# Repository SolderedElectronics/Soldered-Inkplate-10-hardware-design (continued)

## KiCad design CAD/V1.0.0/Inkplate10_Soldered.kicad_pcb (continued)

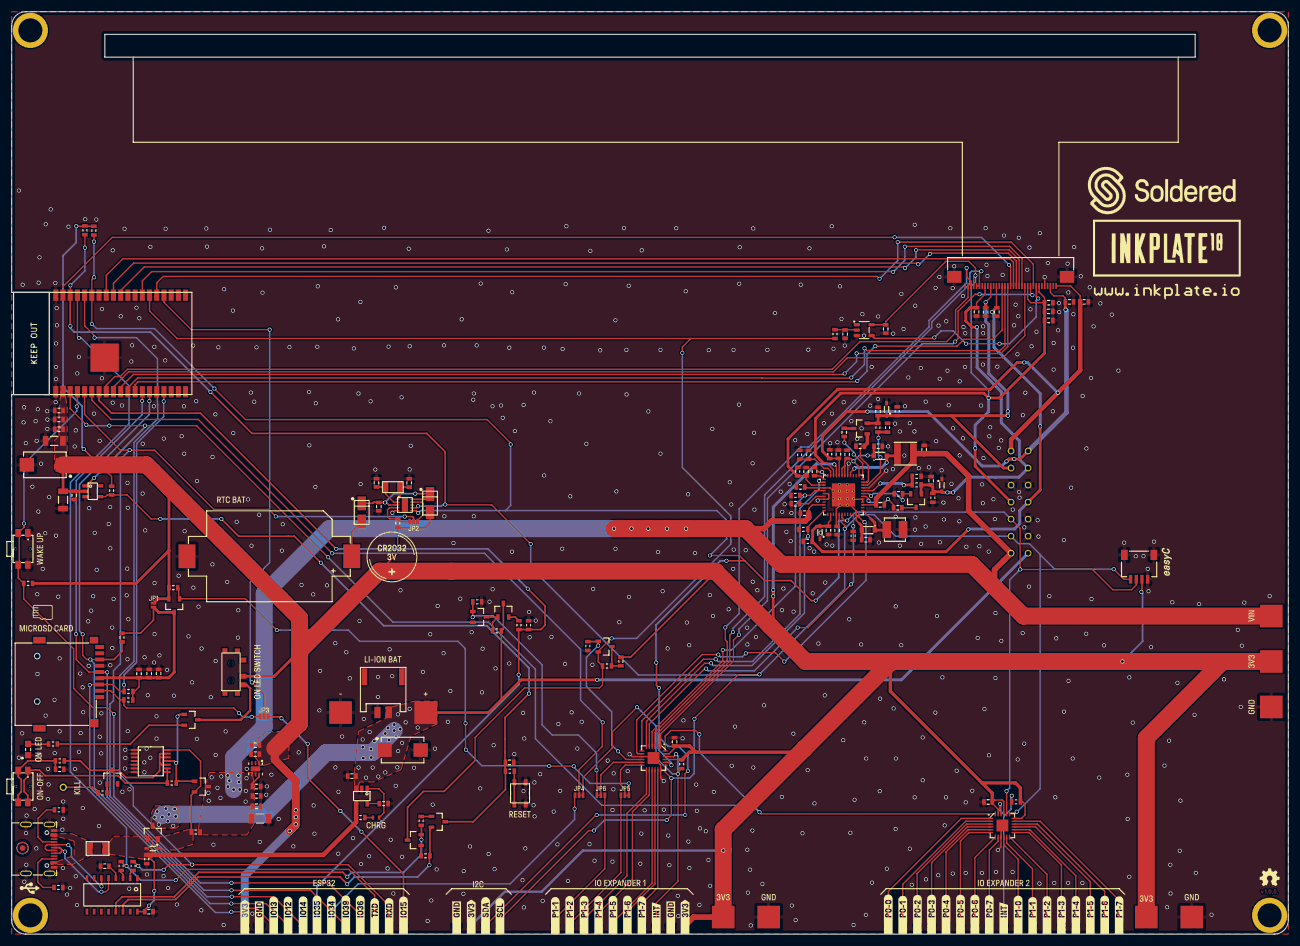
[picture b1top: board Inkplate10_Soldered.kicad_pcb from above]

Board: 2 copper layers, 224.8 x 162.4 mm, 290 parts (1 on the bottom side), 131 nets.

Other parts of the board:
Ref**: Val**; Version1.0.0.
kibuzzard-62EA6F76: G***; kibuzzard-62EA6F76
kibuzzard-62EA6FEE: G***; kibuzzard-62EA6FEE
kibuzzard-62EA71AD: G***; kibuzzard-62EA71AD
kibuzzard-62EA71BF: G***; kibuzzard-62EA71BF
kibuzzard-62EA71CF: G***; kibuzzard-62EA71CF
kibuzzard-62EA72A0: G***; kibuzzard-62EA72A0
kibuzzard-62EA72B5: G***; kibuzzard-62EA72B5
kibuzzard-62EA72C4: G***; kibuzzard-62EA72C4
kibuzzard-62EA72D5: G***; kibuzzard-62EA72D5
kibuzzard-62EA72FE: G***; kibuzzard-62EA72FE
kibuzzard-62EA74CF: G***; kibuzzard-62EA74CF
kibuzzard-62EA713E: G***; kibuzzard-62EA713E
kibuzzard-62EA717A: G***; kibuzzard-62EA717A
kibuzzard-62EA718B: G***; kibuzzard-62EA718B
kibuzzard-62EA719A: G***; kibuzzard-62EA719A
kibuzzard-62EA730E: G***; kibuzzard-62EA730E
kibuzzard-62EA738C: G***; kibuzzard-62EA738C
kibuzzard-62EA7151: G***; kibuzzard-62EA7151
kibuzzard-62EA7167: G***; kibuzzard-62EA7167
kibuzzard-62EA7320: G***; kibuzzard-62EA7320
kibuzzard-62EA7623: G***; kibuzzard-62EA7623
kibuzzard-62EA7653: G***; kibuzzard-62EA7653
kibuzzard-62F64A5D: G***; kibuzzard-62F64A5D
kibuzzard-62F64A9D: G***; kibuzzard-62F64A9D
kibuzzard-62F64A12: G***; kibuzzard-62F64A12
kibuzzard-62F64A79: G***; kibuzzard-62F64A79
kibuzzard-62F64AB0: G***; kibuzzard-62F64AB0
kibuzzard-62F64AD7: G***; kibuzzard-62F64AD7
kibuzzard-62F64B01: G***; kibuzzard-62F64B01
kibuzzard-62F64B1C: G***; kibuzzard-62F64B1C
kibuzzard-62F64B4C: G***; kibuzzard-62F64B4C
kibuzzard-62F64B5B: G***; kibuzzard-62F64B5B
kibuzzard-62F64B36: G***; kibuzzard-62F64B36
kibuzzard-62F64C02: G***; kibuzzard-62F64C02
kibuzzard-62F64ED6: G***; kibuzzard-62F64ED6
kibuzzard-62F64EF1: G***; kibuzzard-62F64EF1
kibuzzard-62F64FB5: G***; kibuzzard-62F64FB5
kibuzzard-62F647A2: G***; kibuzzard-62F647A2
kibuzzard-62F647AE: G***; kibuzzard-62F647AE
kibuzzard-62F647BC: G***; kibuzzard-62F647BC
kibuzzard-62F648C5: G***; kibuzzard-62F648C5
kibuzzard-62F6465B, kibuzzard-62F6465B#2, kibuzzard-62F6465B#3: G***; kibuzzard-62F6465B
kibuzzard-62F6485B: G***; kibuzzard-62F6485B
kibuzzard-62F6487E: G***; kibuzzard-62F6487E
kibuzzard-62F6488E: G***; kibuzzard-62F6488E
kibuzzard-62F6489F: G***; kibuzzard-62F6489F
kibuzzard-62F64634, kibuzzard-62F64634#2, kibuzzard-62F64634#3: G***; kibuzzard-62F64634
kibuzzard-62F64673: G***; kibuzzard-62F64673
kibuzzard-62F64683: G***; kibuzzard-62F64683
kibuzzard-62F64831: G***; kibuzzard-62F64831
kibuzzard-62F64846: G***; kibuzzard-62F64846
kibuzzard-62F64870: G***; kibuzzard-62F64870
kibuzzard-62F64924, kibuzzard-62F64924#2, kibuzzard-62F64924#3: G***; kibuzzard-62F64924
kibuzzard-62F64932, kibuzzard-62F64932#2, kibuzzard-62F64932#3: G***; kibuzzard-62F64932
kibuzzard-110,125: G***; kibuzzard-62F64F49
kibuzzard-63035A45: G***; kibuzzard-63035A45
kibuzzard-63035A96: G***; kibuzzard-63035A96
kibuzzard-630359AB: G***; kibuzzard-630359AB
kibuzzard-6303591E: G***; kibuzzard-6303591E
kibuzzard-63035436: G***; kibuzzard-63035436
kibuzzard-63035904: G***; kibuzzard-63035904
kibuzzard-63035944: G***; kibuzzard-63035944
kibuzzard-63035991: G***; kibuzzard-63035991
kibuzzard-63037233: G***; kibuzzard-63037233

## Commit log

2023-02-01 Updating open source files.
2025-07-09 Update README.md
    Update Tutorials & Projects URL
